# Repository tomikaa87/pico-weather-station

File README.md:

# pico-weather-station
Raspberry Pi Pico-based Internet weather station

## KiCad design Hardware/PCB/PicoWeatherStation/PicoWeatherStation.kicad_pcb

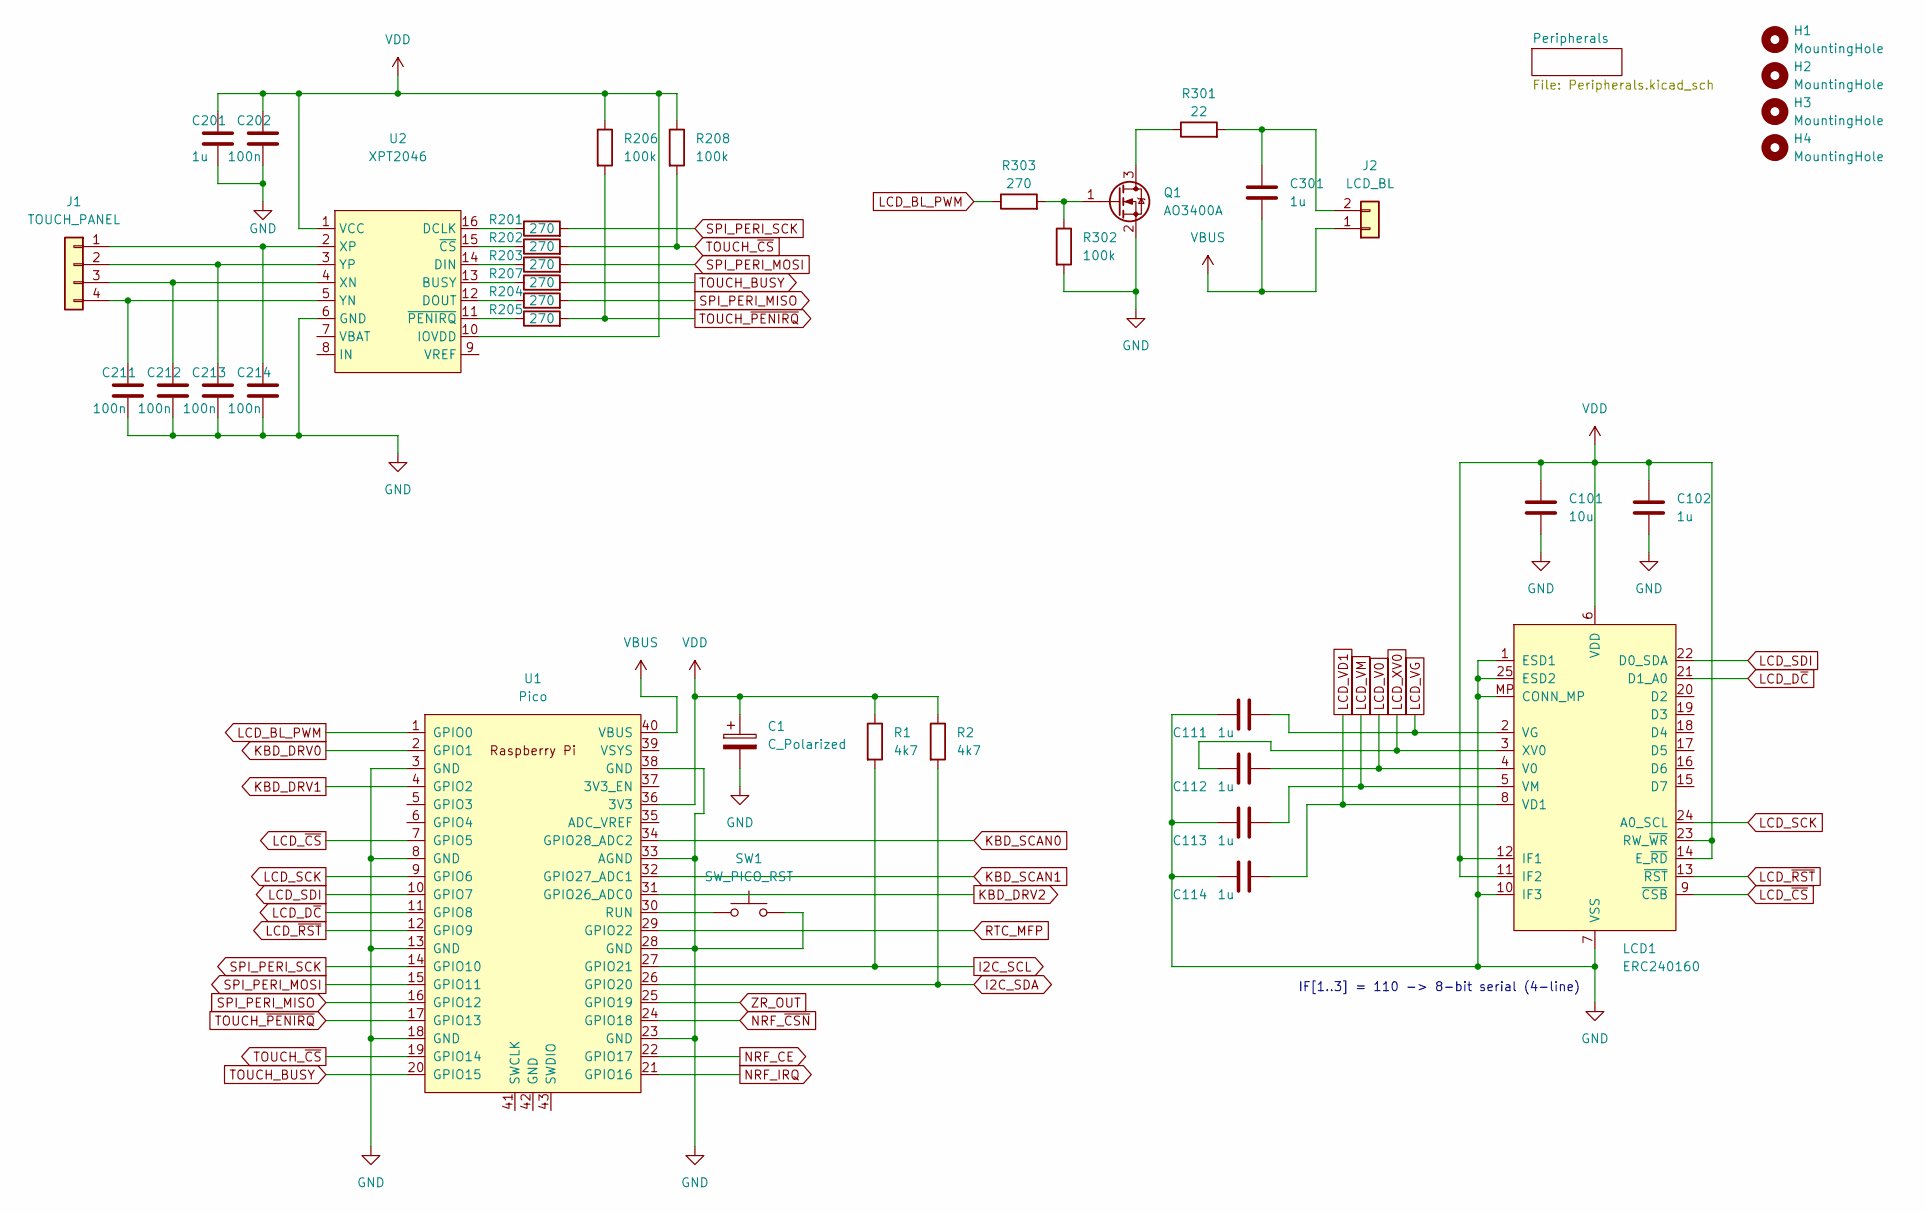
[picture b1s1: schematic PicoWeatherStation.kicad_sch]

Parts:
C1: C_Polarized; CP_Elec_5x5.4
C101: 10u; C_0805_2012Metric_Pad1.18x1.45mm_HandSolder
C102, C111, C112, C113, C114, C201, C301: 1u; C_0805_2012Metric_Pad1.18x1.45mm_HandSolder
C202, C211, C212, C213, C214: 100n; C_0805_2012Metric_Pad1.18x1.45mm_HandSolder
H1, H2, H3, H4: MountingHole; MountingHole_2.7mm_Pad_Via
J1: TOUCH_PANEL; TE_84953-4_1x04-1MP_P1.0mm_Horizontal
J2: LCD_BL; Backlight_Connector_SMD_P2.00mm
LCD1: ERC240160
Q1: AO3400A; SOT-23
R1, R2: 4k7; R_0805_2012Metric_Pad1.20x1.40mm_HandSolder
R201, R202, R203, R204, R205, R207, R303: 270; R_0805_2012Metric_Pad1.20x1.40mm_HandSolder
R206, R208, R302: 100k; R_0805_2012Metric_Pad1.20x1.40mm_HandSolder
R301: 22; R_0805_2012Metric_Pad1.20x1.40mm_HandSolder
SW1: SW_PICO_RST; SW_Push_1P1T_NO_6x6mm_H9.5mm
U1: Pico; RPi_PicoW_SMD
U2: XPT2046; TSSOP-16_4.4x5mm_P0.65mm

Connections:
GND: C1.2, C101.2, C102.2, C111.1, C113.2, C114.1, C201.2, C202.2, C211.2, C212.2, C213.2, C214.2, LCD1.1 (ESD1), LCD1.7 (VSS), LCD1.10 (IF3), LCD1.25 (ESD2), LCD1.MP (CONN_MP), Q1.2 (S), R302.2, SW1.2, U1.3 (GND), U1.8 (GND), U1.13 (GND), U1.18 (GND), U1.23 (GND), U1.28 (GND), U1.33 (AGND), U1.38 (GND), U2.6 (GND); also elsewhere on the board
I2C_SCL: R1.2, U1.27 (GPIO21); also elsewhere on the board
I2C_SDA: R2.2, U1.26 (GPIO20); also elsewhere on the board
KBD_DRV0: U1.2 (GPIO1); also elsewhere on the board
KBD_DRV1: U1.4 (GPIO2); also elsewhere on the board
KBD_DRV2: U1.31 (GPIO26_ADC0); also elsewhere on the board
KBD_SCAN0: U1.34 (GPIO28_ADC2); also elsewhere on the board
KBD_SCAN1: U1.32 (GPIO27_ADC1); also elsewhere on the board
LCD_BL_PWM: R303.1, U1.1 (GPIO0)
LCD_D~C: LCD1.21 (D1_A0), U1.11 (GPIO8)
LCD_SCK: LCD1.24 (A0_SCL), U1.9 (GPIO6)
LCD_SDI: LCD1.22 (D0_SDA), U1.10 (GPIO7)
LCD_V0: C112.2, LCD1.4 (V0)
LCD_VD1: C114.2, LCD1.8 (VD1)
LCD_VG: C111.2, LCD1.2 (VG)
LCD_VM: C113.1, LCD1.5 (VM)
LCD_XV0: C112.1, LCD1.3 (XV0)
LCD_~CS: LCD1.9 (~CSB), U1.7 (GPIO5)
LCD_~RST: LCD1.13 (~RST), U1.12 (GPIO9)
NRF_CE: U1.22 (GPIO17); also elsewhere on the board
NRF_IRQ: U1.21 (GPIO16); also elsewhere on the board
NRF_~CSN: U1.24 (GPIO18); also elsewhere on the board
unnamed: C211.1, J1.4, U2.5 (YN)
unnamed: C212.1, J1.3, U2.4 (XN)
unnamed: C213.1, J1.2, U2.3 (YP)
unnamed: C214.1, J1.1, U2.2 (XP)
unnamed: C301.1, J2.2, R301.2
unnamed: Q1.1 (G), R302.1, R303.2
unnamed: Q1.3 (D), R301.1
unnamed: R201.1, U2.16 (DCLK)
unnamed: R202.1, U2.15 (~CS)
unnamed: R203.1, U2.14 (DIN)
unnamed: R204.1, U2.12 (DOUT)
unnamed: R205.1, U2.11 (~PENIRQ)
unnamed: R207.1, U2.13 (BUSY)
unnamed: SW1.1, U1.30 (RUN)
RTC_MFP: U1.29 (GPIO22); also elsewhere on the board
SPI_PERI_MISO: R204.2, U1.16 (GPIO12); also elsewhere on the board
SPI_PERI_MOSI: R203.2, U1.15 (GPIO11); also elsewhere on the board
SPI_PERI_SCK: R201.2, U1.14 (GPIO10); also elsewhere on the board
TOUCH_BUSY: R207.2, U1.20 (GPIO15)
TOUCH_~CS: R202.2, R208.2, U1.19 (GPIO14)
TOUCH_~PENIRQ: R205.2, R206.2, U1.17 (GPIO13)
VBUS: C301.2, J2.1, U1.40 (VBUS)
VDD: C1.1, C101.1, C102.1, C201.1, C202.1, LCD1.6 (VDD), LCD1.11 (IF2), LCD1.12 (IF1), LCD1.14 (E_~RD), LCD1.23 (RW_~WR), R1.1, R2.1, R206.1, R208.1, U1.36 (3V3), U2.1 (VCC), U2.10 (IOVDD); also elsewhere on the board
ZR_OUT: U1.25 (GPIO19); also elsewhere on the board

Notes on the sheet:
IF[1..3] = 110 -> 8-bit serial (4-line)

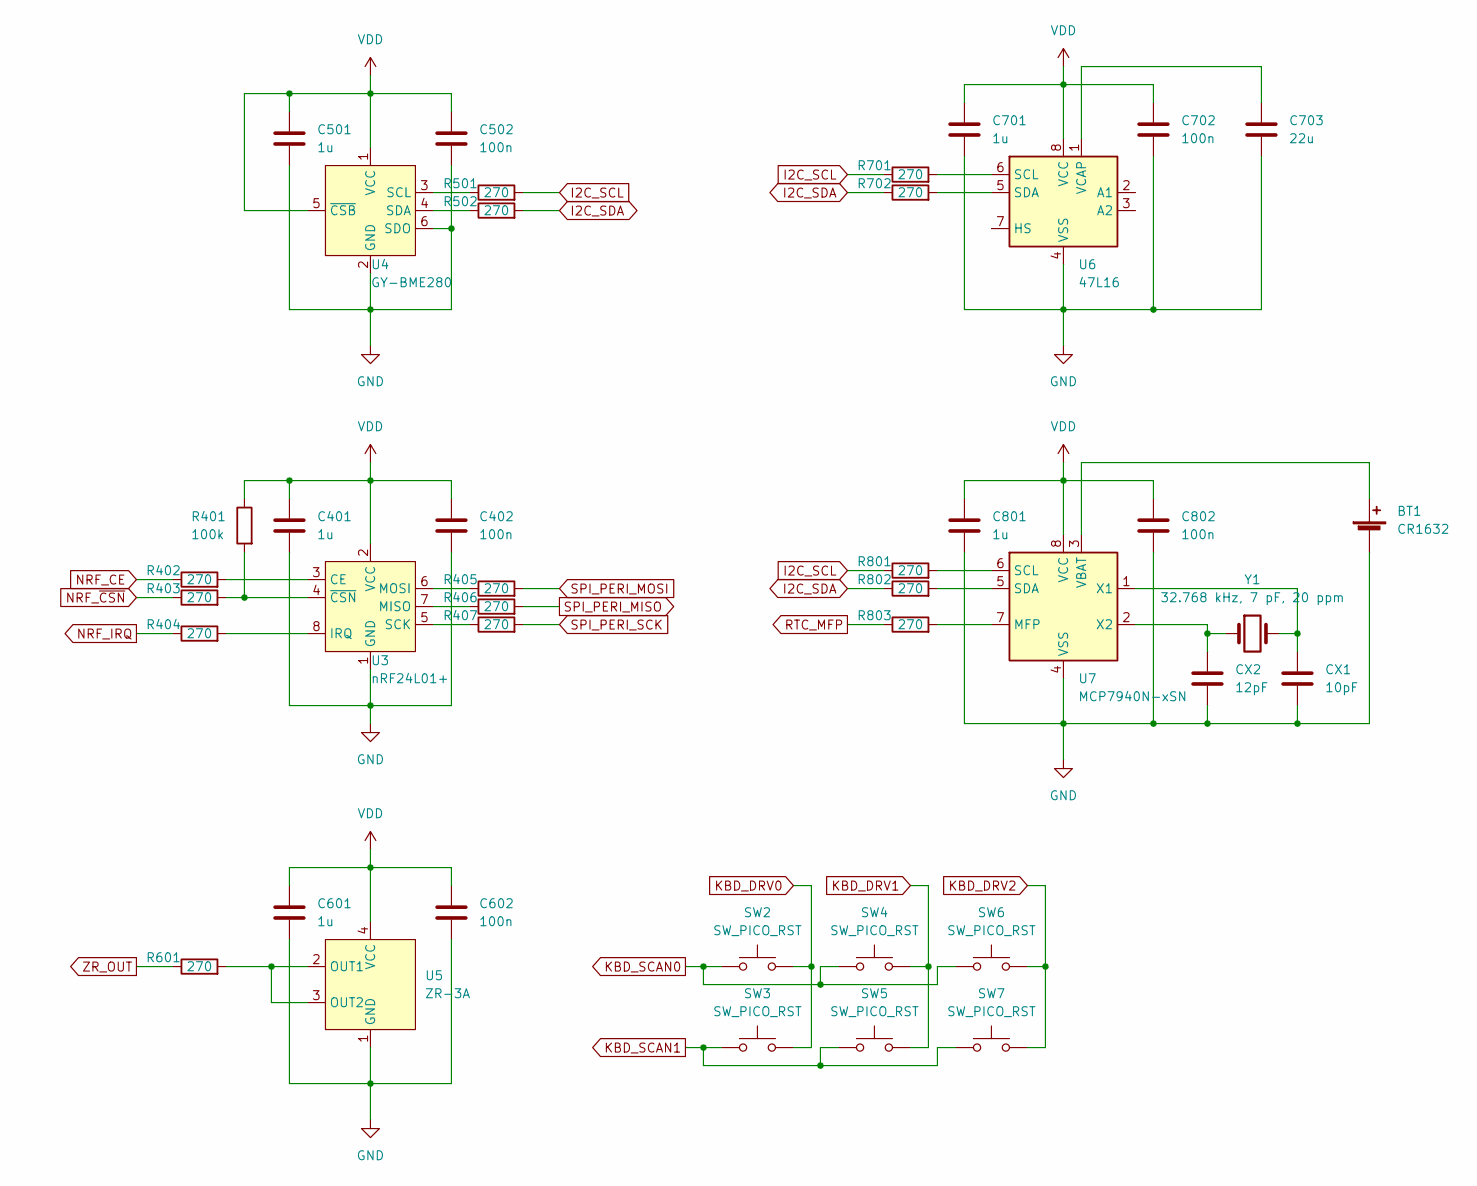
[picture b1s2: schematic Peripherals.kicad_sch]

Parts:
BT1: CR1632; Battery_Holder_CR1632
C401, C501, C601, C701, C801: 1u; C_0805_2012Metric_Pad1.18x1.45mm_HandSolder
C402, C502, C602, C702, C802: 100n; C_0805_2012Metric_Pad1.18x1.45mm_HandSolder
C703: 22u; C_0805_2012Metric_Pad1.18x1.45mm_HandSolder
CX1: 10pF; C_0805_2012Metric_Pad1.18x1.45mm_HandSolder
CX2: 12pF; C_0805_2012Metric_Pad1.18x1.45mm_HandSolder
R401: 100k; R_0805_2012Metric_Pad1.20x1.40mm_HandSolder
R402, R403, R404, R405, R406, R407, R501, R502, R601, R701, R702, R801, R802, R803: 270; R_0805_2012Metric_Pad1.20x1.40mm_HandSolder
SW2, SW3, SW4, SW5, SW6, SW7: SW_PICO_RST; SW_Push_1P1T_NO_6x6mm_H9.5mm
U3: nRF24L01+
U4: GY-BME280
U5: ZR-3A
U6: 47L16; SOIC-8_3.9x4.9mm_P1.27mm
U7: MCP7940N-xSN; SOIC-8_3.9x4.9mm_P1.27mm
Y1: 32.768 kHz, 7 pF, 20 ppm; Crystal_SMD_5032-2Pin_5.0x3.2mm

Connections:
GND: BT1.2 (-), C401.2, C402.2, C501.2, C502.2, C601.2, C602.2, C701.2, C702.2, C703.2, C801.2, C802.2, CX1.2, CX2.2, U3.1 (GND), U4.2 (GND), U4.6 (SDO), U5.1 (GND), U6.4 (VSS), U7.4 (VSS); also elsewhere on the board
I2C_SCL: R501.2, R701.1, R801.1; also elsewhere on the board
I2C_SDA: R502.2, R702.1, R802.1; also elsewhere on the board
KBD_DRV0: SW2.2, SW3.2; also elsewhere on the board
KBD_DRV1: SW4.2, SW5.2; also elsewhere on the board
KBD_DRV2: SW6.2, SW7.2; also elsewhere on the board
KBD_SCAN0: SW2.1, SW4.1, SW6.1; also elsewhere on the board
KBD_SCAN1: SW3.1, SW5.1, SW7.1; also elsewhere on the board
NRF_CE: R402.1; also elsewhere on the board
NRF_IRQ: R404.1; also elsewhere on the board
NRF_~CSN: R403.1; also elsewhere on the board
unnamed: BT1.1 (+), U7.3 (VBAT)
unnamed: C703.1, U6.1 (VCAP)
unnamed: CX1.1, U7.1 (X1), Y1.2
unnamed: CX2.1, U7.2 (X2), Y1.1
unnamed: R401.2, R403.2, U3.4 (~CSN)
unnamed: R402.2, U3.3 (CE)
unnamed: R404.2, U3.8 (IRQ)
unnamed: R405.1, U3.6 (MOSI)
unnamed: R406.1, U3.7 (MISO)
unnamed: R407.1, U3.5 (SCK)
unnamed: R501.1, U4.3 (SCL)
unnamed: R502.1, U4.4 (SDA)
unnamed: R601.2, U5.2 (OUT1), U5.3 (OUT2)
unnamed: R701.2, U6.6 (SCL)
unnamed: R702.2, U6.5 (SDA)
unnamed: R801.2, U7.6 (SCL)
unnamed: R802.2, U7.5 (SDA)
unnamed: R803.2, U7.7 (MFP)
RTC_MFP: R803.1; also elsewhere on the board
SPI_PERI_MISO: R406.2; also elsewhere on the board
SPI_PERI_MOSI: R405.2; also elsewhere on the board
SPI_PERI_SCK: R407.2; also elsewhere on the board
VDD: C401.1, C402.1, C501.1, C502.1, C601.1, C602.1, C701.1, C702.1, C801.1, C802.1, R401.1, U3.2 (VCC), U4.1 (VCC), U4.5 (~CSB), U5.4 (VCC), U6.8 (VCC), U7.8 (VCC); also elsewhere on the board
ZR_OUT: R601.1; also elsewhere on the board

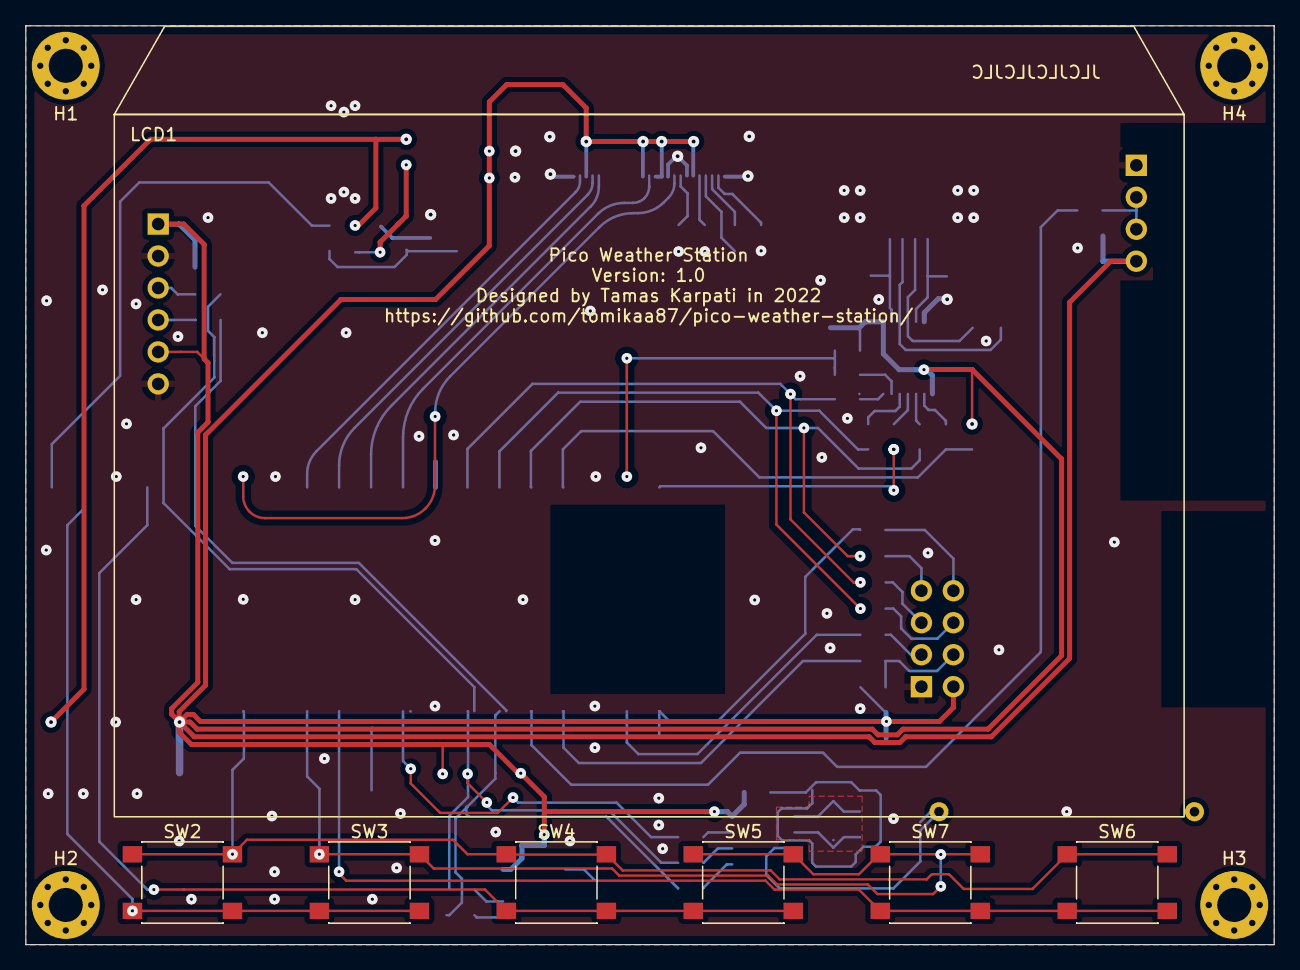
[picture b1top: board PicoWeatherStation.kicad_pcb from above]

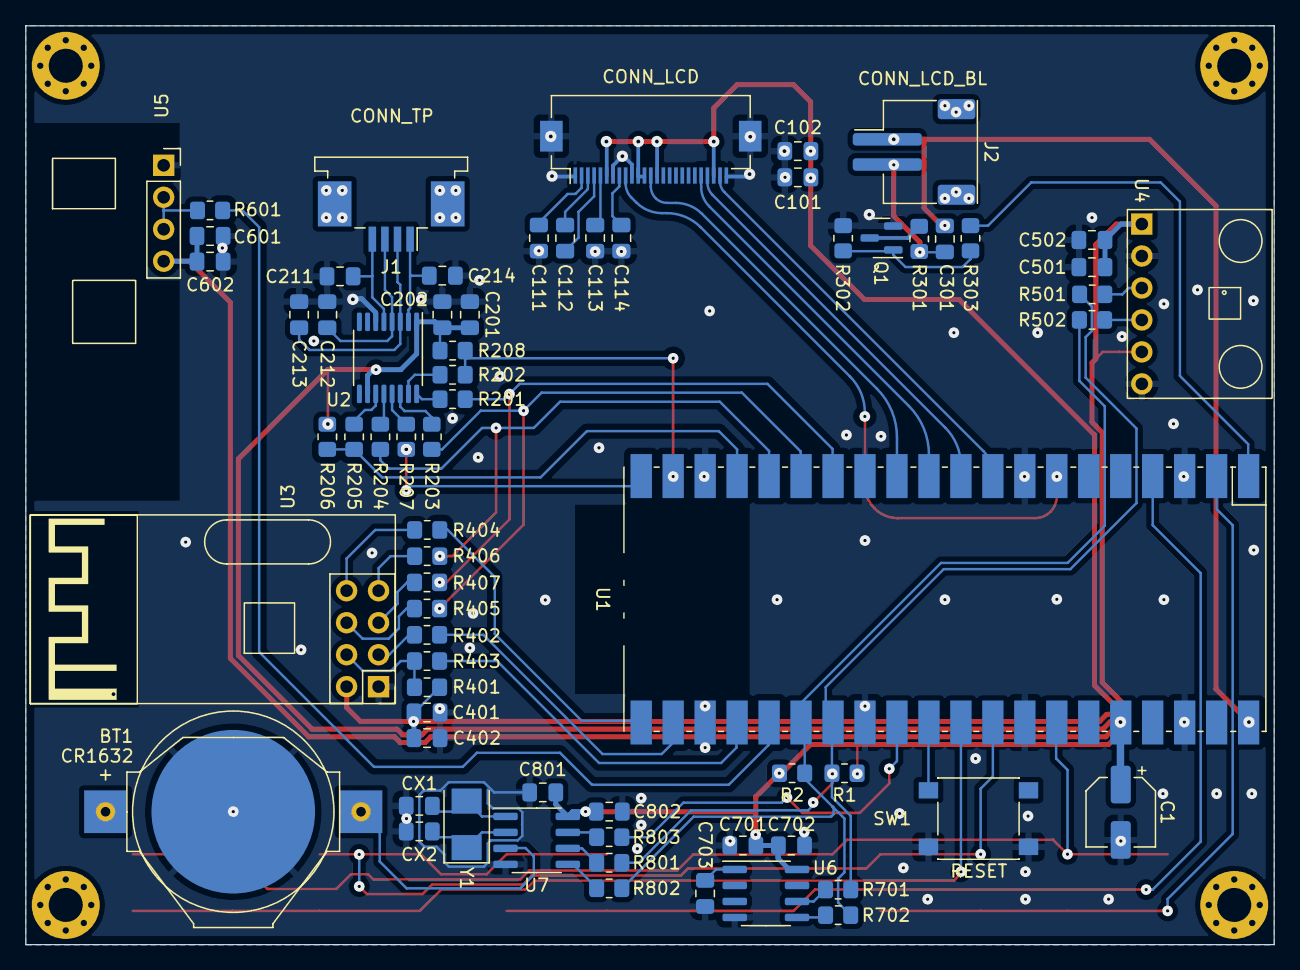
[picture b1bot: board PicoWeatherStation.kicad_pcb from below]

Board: 2 copper layers, 99.2 x 73.0 mm, 79 parts (68 on the bottom side), 64 nets.

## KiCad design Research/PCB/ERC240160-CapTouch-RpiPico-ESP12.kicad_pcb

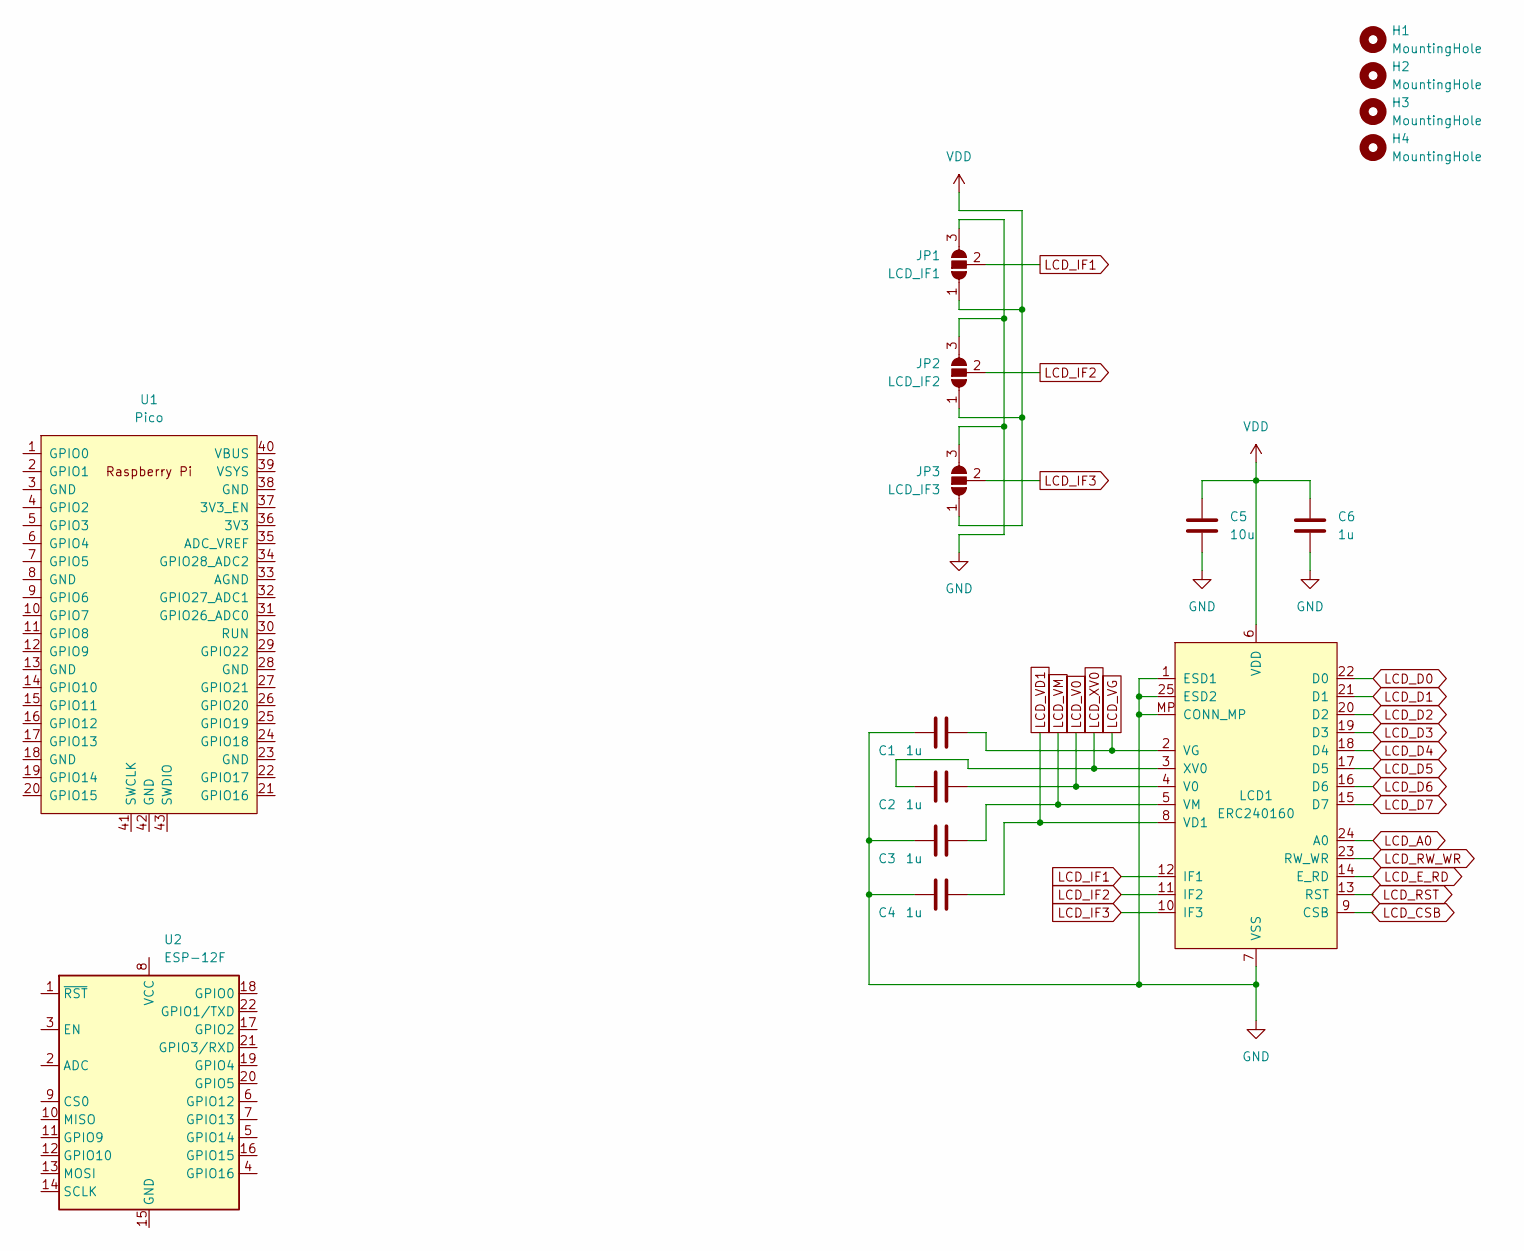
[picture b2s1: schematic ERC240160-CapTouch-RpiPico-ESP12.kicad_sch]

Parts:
C1, C2, C3, C4, C6: 1u; C_0805_2012Metric_Pad1.18x1.45mm_HandSolder
C5: 10u; C_0805_2012Metric_Pad1.18x1.45mm_HandSolder
H1, H2, H3, H4: MountingHole; MountingHole_3.2mm_M3_Pad_Via
JP1: LCD_IF1; SolderJumper-3_P2.0mm_Open_TrianglePad1.0x1.5mm_NumberLabels
JP2: LCD_IF2; SolderJumper-3_P2.0mm_Open_TrianglePad1.0x1.5mm_NumberLabels
JP3: LCD_IF3; SolderJumper-3_P2.0mm_Open_TrianglePad1.0x1.5mm_NumberLabels
LCD1: ERC240160
U1: Pico; RPi_Pico_SMD
U2: ESP-12F; ESP-12E

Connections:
GND: C1.1, C3.2, C4.1, C5.2, C6.2, JP1.3 (B), JP2.3 (B), JP3.3 (B), LCD1.1 (ESD1), LCD1.7 (VSS), LCD1.25 (ESD2), LCD1.MP (CONN_MP)
LCD_A0: LCD1.24 (A0)
LCD_CSB: LCD1.9 (CSB)
LCD_D0: LCD1.22 (D0)
LCD_D1: LCD1.21 (D1)
LCD_D2: LCD1.20 (D2)
LCD_D3: LCD1.19 (D3)
LCD_D4: LCD1.18 (D4)
LCD_D5: LCD1.17 (D5)
LCD_D6: LCD1.16 (D6)
LCD_D7: LCD1.15 (D7)
LCD_E_RD: LCD1.14 (E_RD)
LCD_IF1: JP1.2 (C), LCD1.12 (IF1)
LCD_IF2: JP2.2 (C), LCD1.11 (IF2)
LCD_IF3: JP3.2 (C), LCD1.10 (IF3)
LCD_RST: LCD1.13 (RST)
LCD_RW_WR: LCD1.23 (RW_WR)
LCD_V0: C2.2, LCD1.4 (V0)
LCD_VD1: C4.2, LCD1.8 (VD1)
LCD_VG: C1.2, LCD1.2 (VG)
LCD_VM: C3.1, LCD1.5 (VM)
LCD_XV0: C2.1, LCD1.3 (XV0)
VDD: C5.1, C6.1, JP1.1 (A), JP2.1 (A), JP3.1 (A), LCD1.6 (VDD)

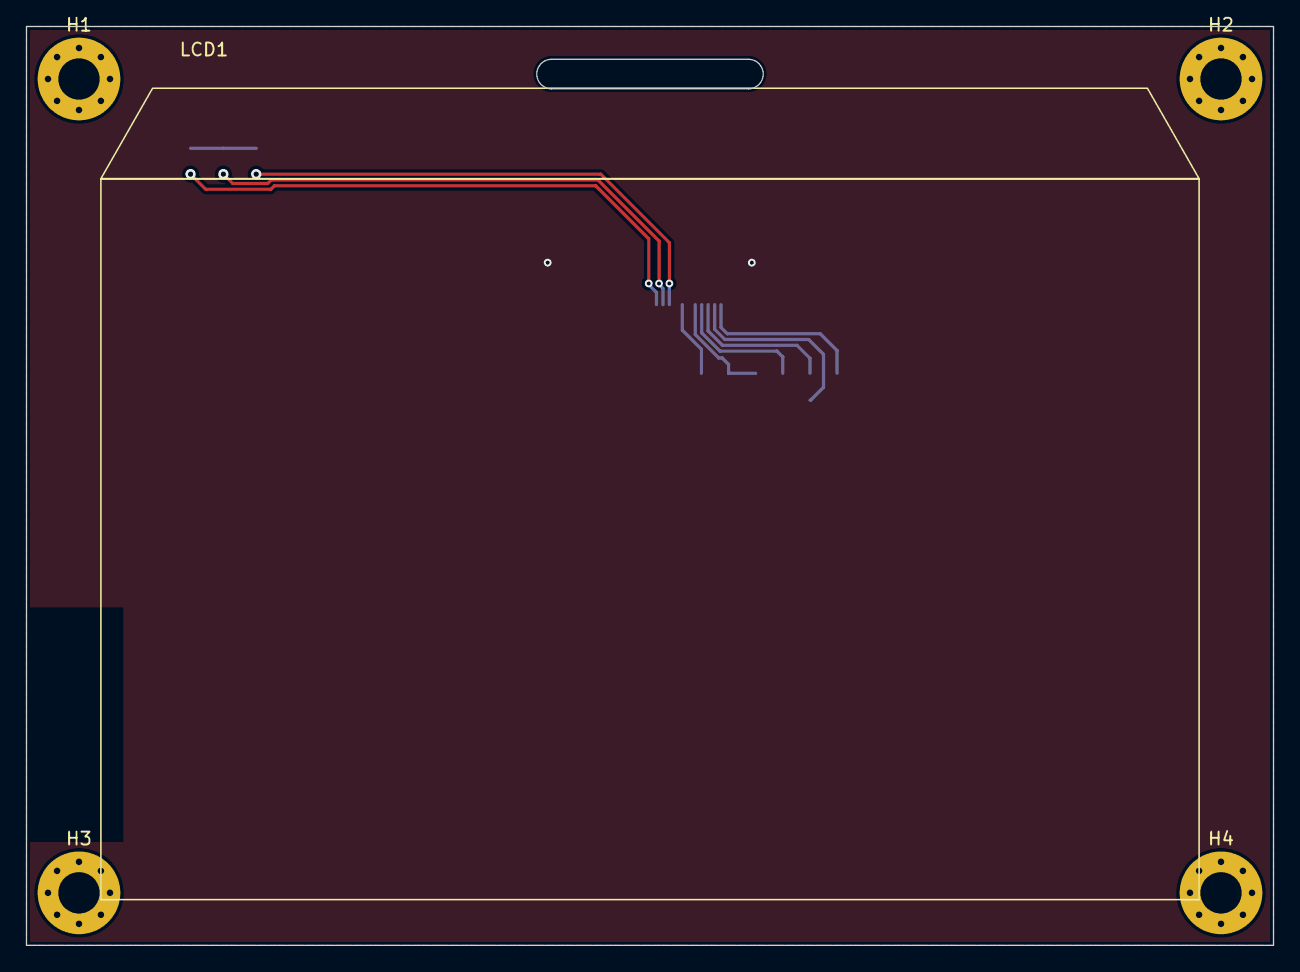
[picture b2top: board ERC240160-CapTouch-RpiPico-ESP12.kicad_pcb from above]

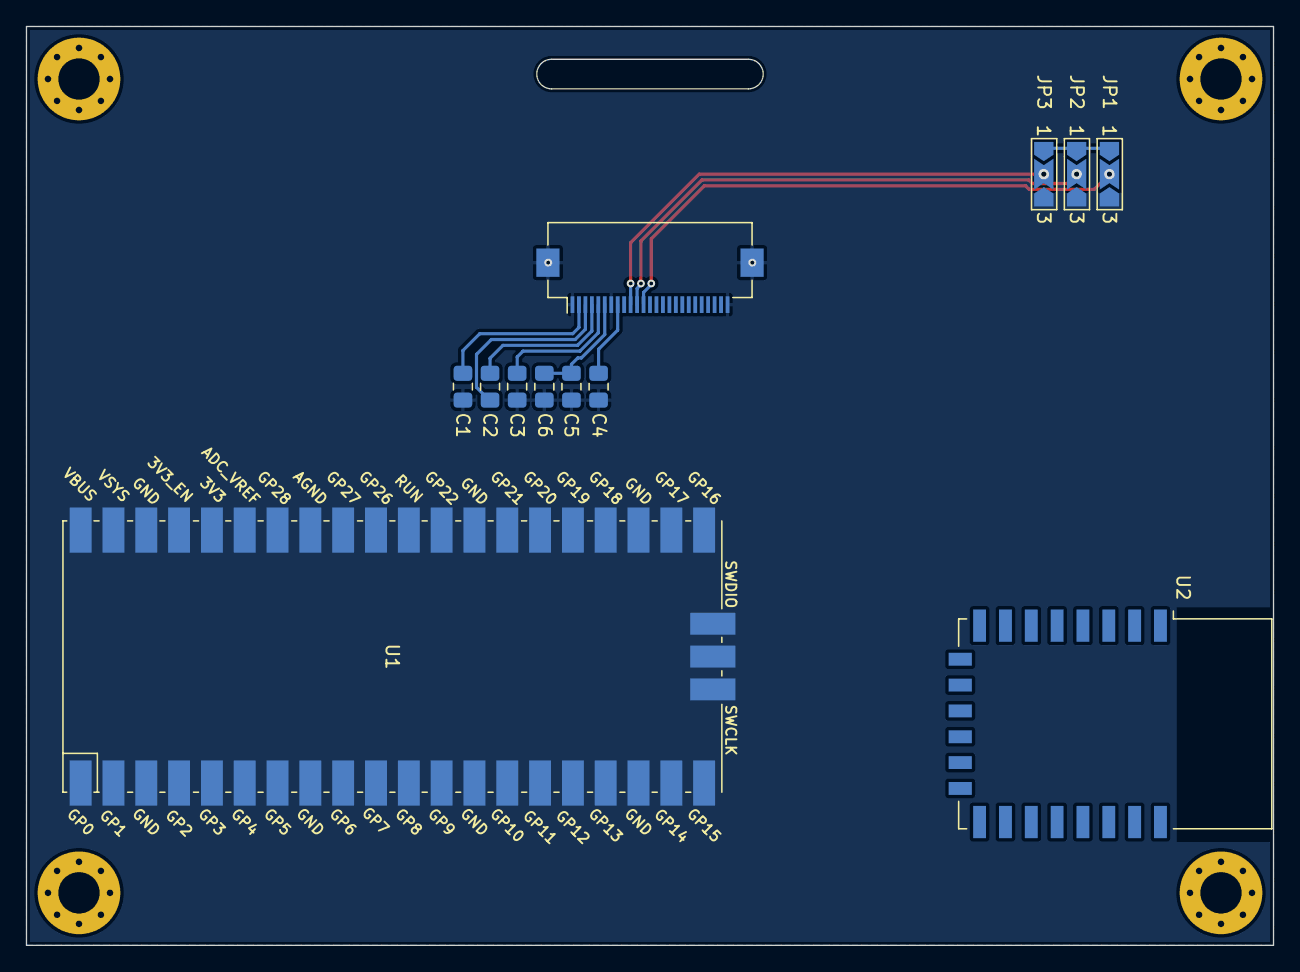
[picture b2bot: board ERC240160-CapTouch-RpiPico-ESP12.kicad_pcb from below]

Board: 2 copper layers, 96.5 x 71.1 mm, 16 parts (11 on the bottom side), 10 nets.

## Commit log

2022-01-12 Research some pixel fonts
2022-01-12 Create an early block diagram
2022-01-12 Add an early main screen photoshop design
2022-01-12 Add documents for the graphic LCD
2022-01-13 Initial commit of schematics and PCB design
2022-01-15 Add 3D model for the Pico
2022-01-15 Add 3D model for the FPC-25 connector
2022-01-15 Add prettier 3D model for the Pico
2022-02-16 Add front-end playground code
2022-02-16 Remove generated executable
2022-02-16 Extract fonts from main.cpp
2022-02-16 Add FMT lib, extract graphics
2022-02-16 Extract display code
2022-02-16 Add more display operations and font support
2022-02-16 Implement basic widget support
2022-02-16 Implement widget clipping
2022-02-16 Implement basic label
2022-02-18 Implement Image widget, clipping to parent rect
2022-02-18 Optimize painting, implement background clearing
2022-02-18 Optimize display updates in Painter
2022-02-18 Improve Label rect calculation
2022-02-19 Add more fonts
2022-02-19 Add weather icons
2022-02-19 Implement image inversion support
2022-02-19 Fix recursive image painting
2022-02-19 Add XBM icons
2022-02-19 Add MainScreen, new fonts, painter debug
2022-02-19 Implement different height calculation methods in Label
2022-02-19 Main screen design test
2022-02-19 Improved main screen design
2022-02-19 Add new fonts
2022-02-20 Improve main screen layout
2022-02-20 Update MainScreenTest image
2022-02-20 Start to populate the main screen with real values
2022-02-21 Improve Point, Size, Rect; add more Main Screen labels
2022-02-22 Fix clock date label clipping
2022-02-22 Add internal sensor data labels to MainScreen
2022-02-22 Implement the graphs on MainScreen
2022-02-22 Implement the forecast widgets on MainScreen
2022-02-22 Add current min/max temp labels to MainScreen
2022-02-22 Fix internal temperature sensor labels on MainScreen
2022-02-26 Restore normal colors
2022-02-26 Implement setting the clock on MainScreen
2022-02-26 Rename MainScreen to WeatherStation
2022-02-26 Add flatbuffers
2022-09-19 Add implementation for Pico
2022-09-19 Use chunked display data transfer with the Pico too
2022-09-21 Add LCD draw performance test
2022-09-21 Initial commit of PCB design
2022-09-21 Add BitCell-Regular-16 font files
2022-09-24 Fully wire up the PCB
2022-09-25 FrontEnd: remap SPI0 pins for the LCD
2022-09-26 Update the PCB
2022-09-26 FrontEnd: add test code for the NRF24 and the BME280
2022-09-27 PCB: add RTC and EERAM
2022-09-27 PCB: wire-up the keyboard
2022-09-28 PCB: optimize high speed LCD signal tracks
2022-09-28 PCB: do minor track optimization
2022-09-28 PCB: optimize peripheral SPI signals
2022-09-28 PCB: bigger footprint for the clock crystal
2022-09-29 PCB: prepare for manufacturing
2022-10-02 Initial commit of 47xxx EERAM driver
2022-10-02 Fix minor issues in the 47xxx EERAM driver
2022-10-03 47xxx: implement GetEVENT()
2022-10-03 47xxx: move register addresses into the C file
2022-10-03 MCP7940N: initial commit
2022-10-06 MCP7940N: implement alarm functions
2022-10-15 Start building the disgnostics screen
2022-10-15 Add NRF24 status to the diag screen
2022-10-15 More readable NRF24 status to the diag screen
2022-10-15 Try to make the touch controller work
2022-10-17 MCP7940N: implement most of the functions
2022-10-18 MCP7940N: implement reading power fail timestamps
2022-10-20 Implement RTC test
2022-10-27 47lxx: rewrite functions with the modified I2C API
2022-10-27 47lxx: add test but it is not working yet
2022-10-28 Add RTC/EERAM test program
2022-10-28 rtc-eeram: add EERAM test and fix the EERAM driver
2022-10-28 Fix EERAM driver
2022-10-28 rtc-eeram: use the original driver files instead of copies
2022-10-28 Initial commit of pico-sdk-based software
2022-10-28 Start replacing Arduino code
2022-10-29 Fix compilation issues
2022-10-29 Fix remaining compilation and linking issues
2022-10-30 Fix peripheral issues, BME280 still unusable
2022-10-30 Fix BME280 driver
2022-10-30 Extract BME280 handling into EvnironmentSensor
2022-10-30 Fiddle with the touch controller
2022-10-30 Start putting the weather screen together
2022-10-30 Fix reading of the touch controller
2022-10-31 MCP7940N: add checks and fix power fail timestamp reading
2022-11-20 Implement reading of EWS2 external sensor
2022-11-20 Implement the keypad driver
2023-07-07 Fix build issues
2023-07-07 WiFi connection PoC
2023-07-07 HTTP request PoC
2023-07-07 OpenWeatherMap API request PoC
2023-07-08 Add lwip and mbedtls config files
2023-07-20 Remove platform.io project files
2023-07-20 Revert "Remove platform.io project files"
    This reverts commit 8f2133b36c09f4ae34d6988e27219d415f750669.
2023-07-20 Bump minimum pico-sdk version
2023-07-20 Start implementing modern network abstractions
2023-07-21 Do some code clean-up
2023-07-21 Implement TcpSocket::disconnect
2023-07-21 Implement TCP read and write
2023-07-30 Add simple-http-parser playground project
